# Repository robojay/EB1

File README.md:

## EB1 电脑一号：A self-contained learning platform.

The Electric Brain 1 (EB1) 电脑一号 is a simple yet surprisingly capable microprocessor and electronics learning tool.

Photo: [EB1 电脑一号](http://www.samuraicircuits.com/MediaWiki/images/7/71/EB1_600_179.jpg)

Example Videos: [YouTube](https://www.youtube.com/playlist?list=PLsja6VAzoAFjkEiDmtCvSfQOGpww-VMCa)

KiCad Schematic and PCB files: [GitHub](https://github.com/robojay/EB1/)

Firmware: *Under Development.*  It is possible to use firmware from similar open source designs. However, we have obtained our own USB PID through [pid.codes](http://pid.codes) and any EB1 released to the public will use this. **You MUST obtain your own USB VID/PID for your projects unless you are using an EB1 manufactured by us. You MAY NOT release products using our USB VID/PID.**

Arduino IDE Compatibility: *Under Development.*  We are currently testing with Version 1.6.3 of the [Official Arduino IDE](http://arduino.cc). Installation instructions and files will be provided soon. The first releases will be "hacker friendly" but not necessarily ready for the general public.

Wiki: [EB1 电脑一号](http://www.samuraicircuits.com/MediaWiki/index.php?title=EB1) 

----

### Please note:

This is still under development and the design definitely contains errors!  

**Use at your own risk, and we are not providing ANY user support at this time!**

### License

This project is licensed as [CC-BY-SA 3.0](http://creativecommons.org/licenses/by-sa/3.0/cn/) . **You are free** to read, study, modify, redistribute, and create products out of our designs **as long as you** distribute your derivative work under the **same license** **and** **attribute to us** the original design.

[Creative Commons 3.0 Attribution, Sharealike](http://creativecommons.org/licenses/by-sa/3.0/cn/)

### Attributions / Inspirations

Although the general idea for this project was conceived many years ago, its implementation was greatly assisted by the work of [Adafruit](http://www.adafruit.com) ([Trinket Bootloader](https://github.com/adafruit/Adafruit-Trinket-Gemma-Bootloader), [Trinket](https://learn.adafruit.com/introducing-trinket/introduction)), [Digispark](http://digistump.com/products/1), [MIT high-low tech](http://highlowtech.org), and all the other folks who have developed/contributed to USB implementation on the Atmel ATtiny processors.

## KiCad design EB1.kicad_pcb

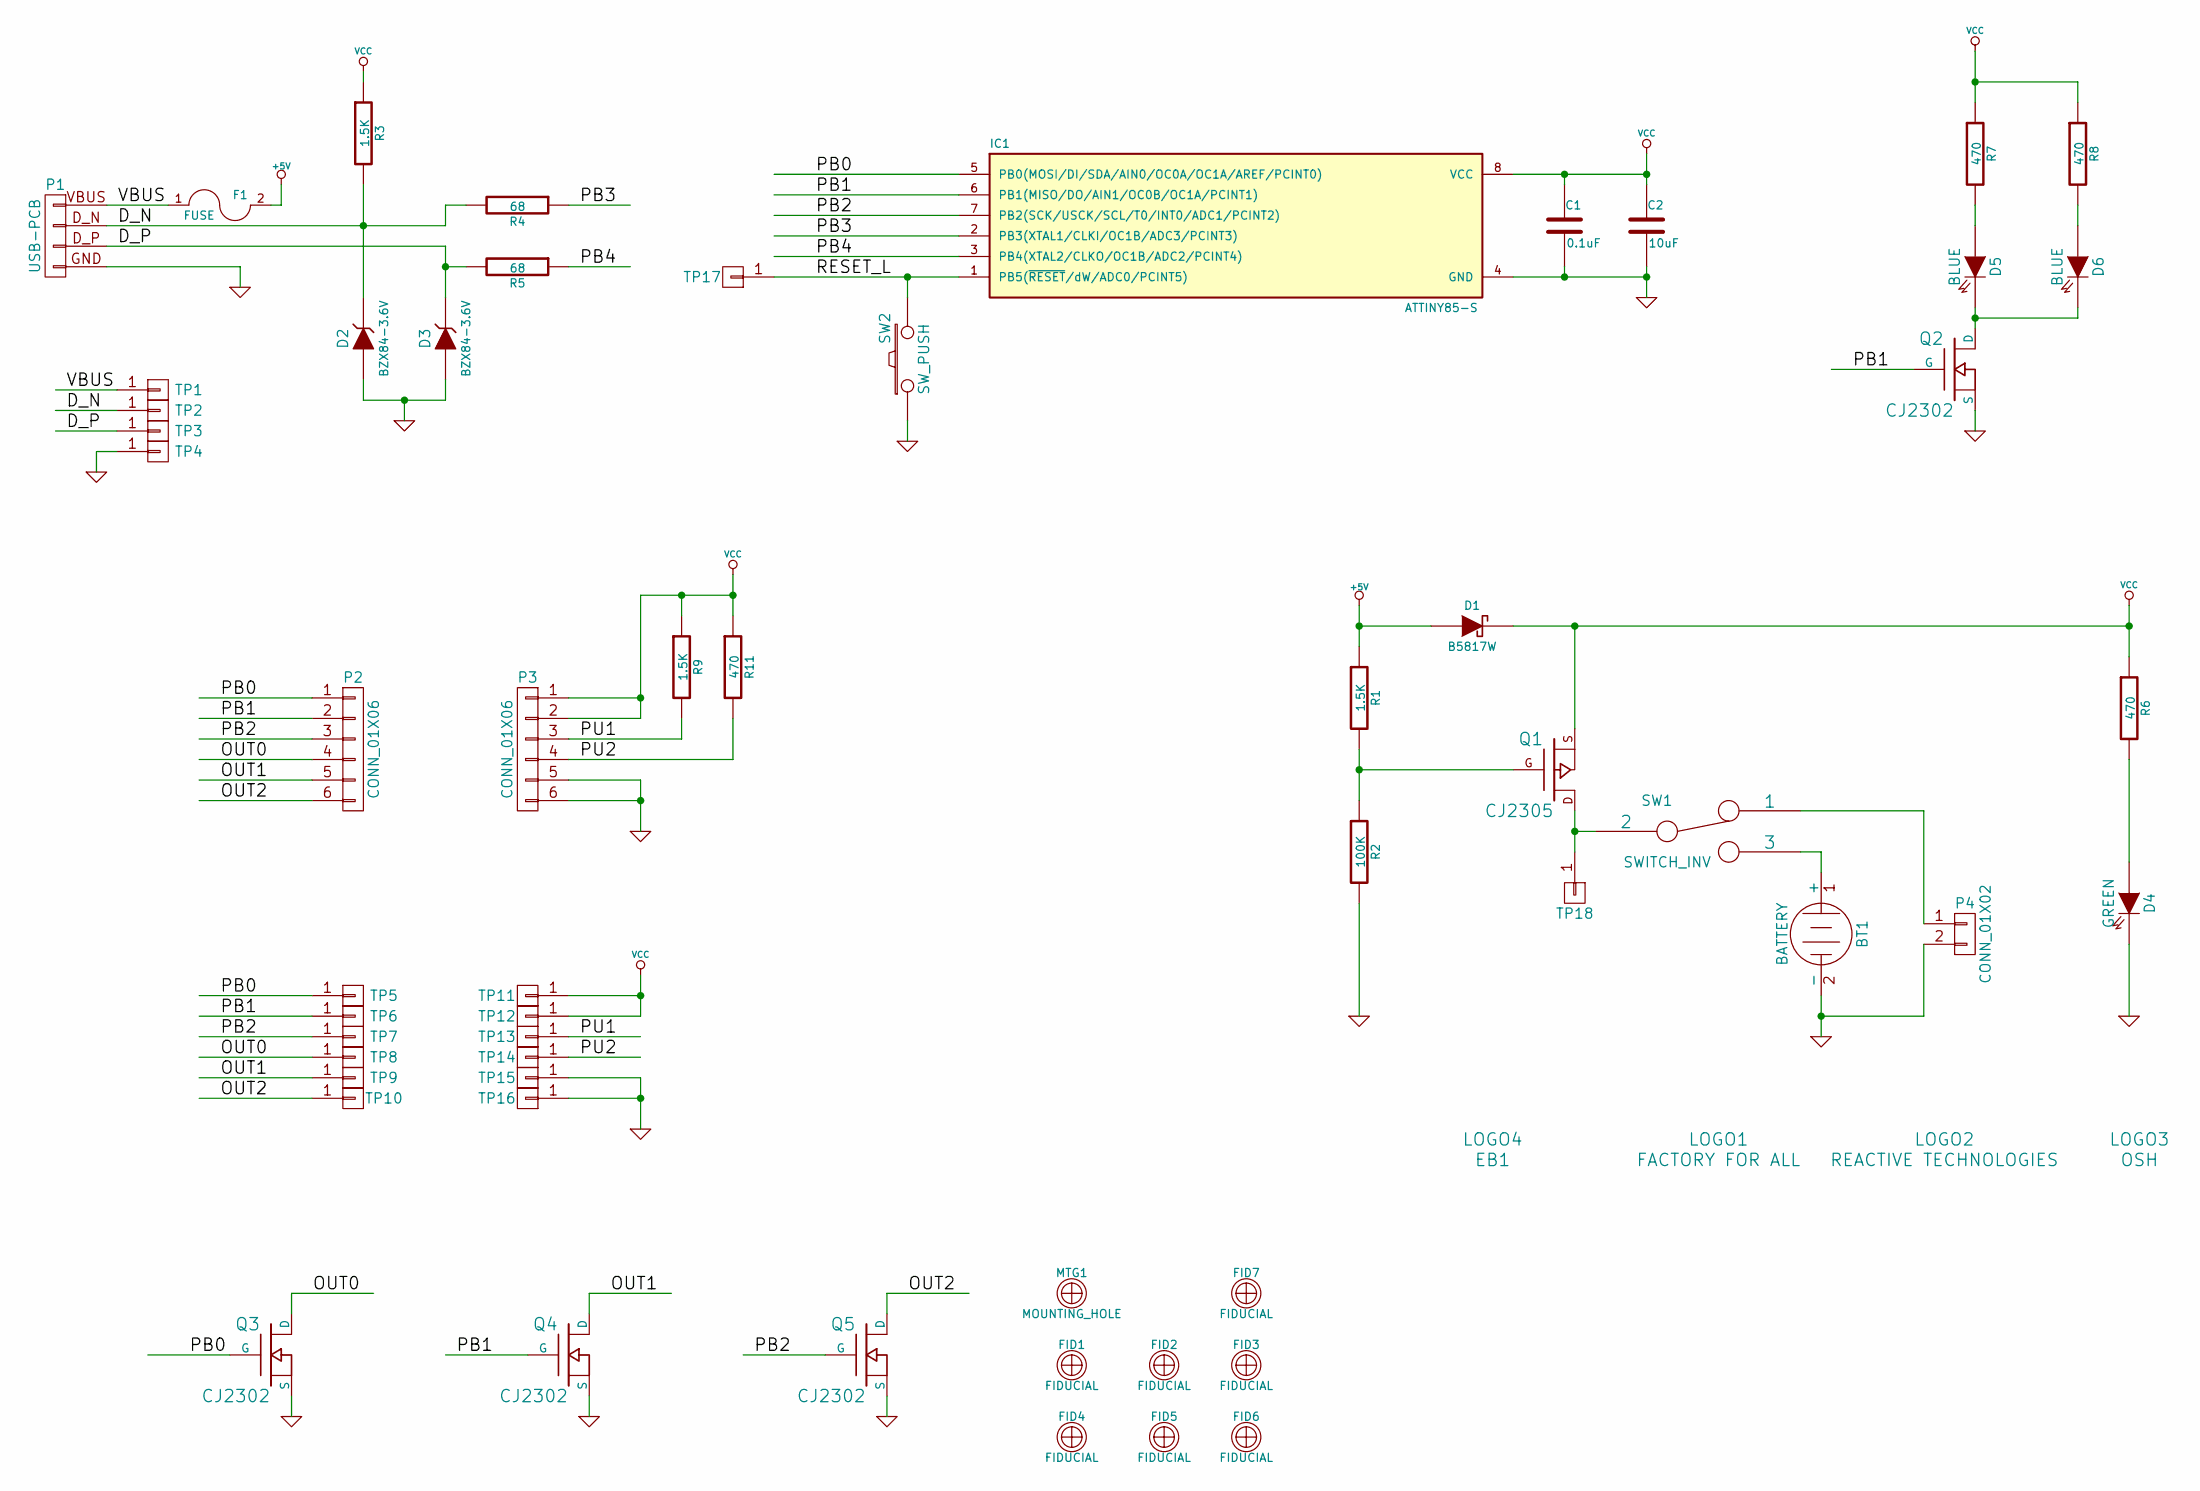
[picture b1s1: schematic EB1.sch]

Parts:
BT1: BATTERY; BS-6
C1: 0.1uF; C_0603
C2: 10uF; C_0603
D1: B5817W; SOD-123
D2, D3: BZX84-3.6V; SOT-23-AXC
D4: GREEN; LED-0805
D5, D6: BLUE; LED-0805
F1: FUSE; Fuse_SMD1206
FID1, FID2, FID3, FID4, FID5, FID6, FID7: FIDUCIAL; FIDUCIAL_1MM_2MM
IC1: ATTINY85-S; SOIC-8-W
LOGO1: FACTORY FOR ALL; Logo_Factory_For_All-0
LOGO2: REACTIVE TECHNOLOGIES; RT_F.SilkS_.6in
LOGO3: OSH; osh-logo-no-name
LOGO4: EB1; EB-Logo
MTG1: MOUNTING_HOLE; HOLE_3MM_3-5MM_CLEAR
P1: USB-PCB; USB-A-PCB
P2, P3: CONN_01X06; SAMTEC_SSM-106
P4: CONN_01X02; Pin_Header_Straight_1x02
Q1: CJ2305; SOT-23-GSD
Q2, Q3, Q4, Q5: CJ2302; SOT-23-GSD
R1, R3, R9: 1.5K; R_0603
R2: 100K; R_0603
R4, R5: 68; R_0603
R6, R7, R8, R11: 470; R_0603
SW1: SWITCH_INV; MS12D17
SW2: SW_PUSH; OMRON_B3U-1000P
TP1, TP2, TP3, TP4, TP5, TP6, TP7, TP8, TP9, TP10, TP11, TP12, TP13, TP14, TP15, TP16, TP17, TP18: CONN_01X01; TESTPOINT_TH

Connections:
+5V: D1.A, F1.2, R1.1
/D_N: D2.C, P1.D_N, R3.2, R4.2, TP2.1
/D_P: D3.C, P1.D_P, R5.2, TP3.1
/OUT0: P2.4, Q3.D, TP8.1
/OUT1: P2.5, Q4.D, TP9.1
/OUT2: P2.6, Q5.D, TP10.1
/PB0: IC1.5 (PB0(MOSI/DI/SDA/AIN0/OC0A/OC1A/AREF/PCI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), P2.1, Q3.G, TP5.1
/PB1: IC1.6 (PB1(MISO/DO/AIN1/OC0B/OC1A/PCINT1)), P2.2, Q2.G, Q4.G, TP6.1
/PB2: IC1.7 (PB2(SCK/USCK/SCL/T0/INT0/ADC1/PCINT2)), P2.3, Q5.G, TP7.1
/PB3: IC1.2 (PB3(XTAL1/CLKI/OC1B/ADC3/PCINT3)), R4.1
/PB4: IC1.3 (PB4(XTAL2/CLKO/OC1B/ADC2/PCINT4)), R5.1
/PU1: P3.3, R9.2, TP13.1
/PU2: P3.4, R11.2, TP14.1
/RESET_L: IC1.1 (PB5(~RESET~/dW/ADC0/PCINT5)), SW2.2, TP17.1
/VBUS: F1.1, P1.VBUS, TP1.1
GND: BT1.2 (-), C1.2, C2.2, D2.A, D3.A, D4.C, IC1.4 (GND), P1.GND, P3.5, P3.6, P4.2, Q2.S, Q3.S, Q4.S, Q5.S, R2.2, SW2.1, TP4.1, TP15.1, TP16.1
unnamed: BT1.1 (+), SW1.3
unnamed: D4.A, R6.2
unnamed: D5.A, R7.2
unnamed: D5.C, D6.C, Q2.D
unnamed: D6.A, R8.2
unnamed: P4.1, SW1.1
unnamed: Q1.D, SW1.2, TP18.1
unnamed: Q1.G, R1.2, R2.1
VCC: C1.1, C2.1, D1.C, IC1.8 (VCC), P3.1, P3.2, Q1.S, R3.1, R6.1, R7.1, R8.1, R9.1, R11.1, TP11.1, TP12.1

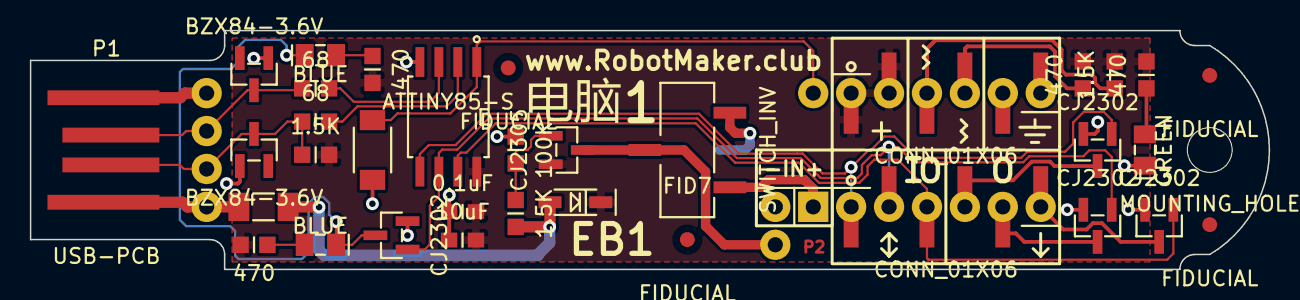
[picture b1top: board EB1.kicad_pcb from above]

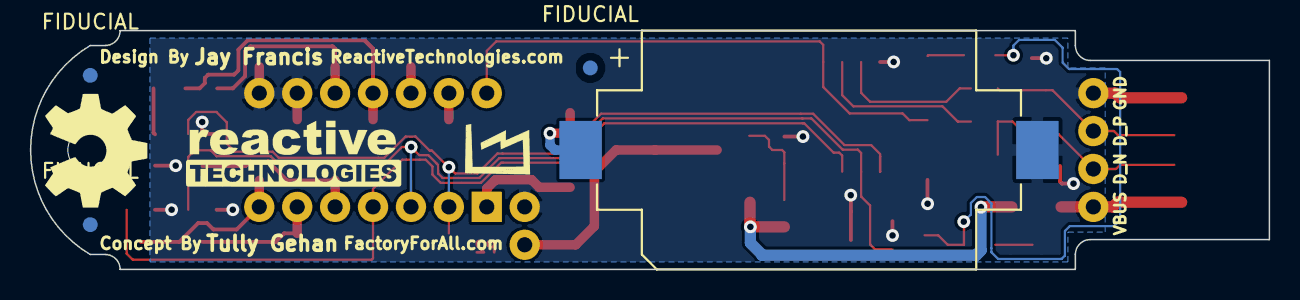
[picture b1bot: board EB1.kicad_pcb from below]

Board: 2 copper layers, 83.0 x 16.0 mm, 62 parts (7 on the bottom side), 25 nets.

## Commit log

2015-04-14 Initial Push
2015-04-14 Initial creation - derived from the EB1 Wiki
